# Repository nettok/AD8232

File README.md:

# AD8232
Single Lead Heart Rate Monitor Circuit Board

DO NOT USE!  This is just an exercise on building a simple PCB based on the following original board from SparkFun: https://www.sparkfun.com/products/12650

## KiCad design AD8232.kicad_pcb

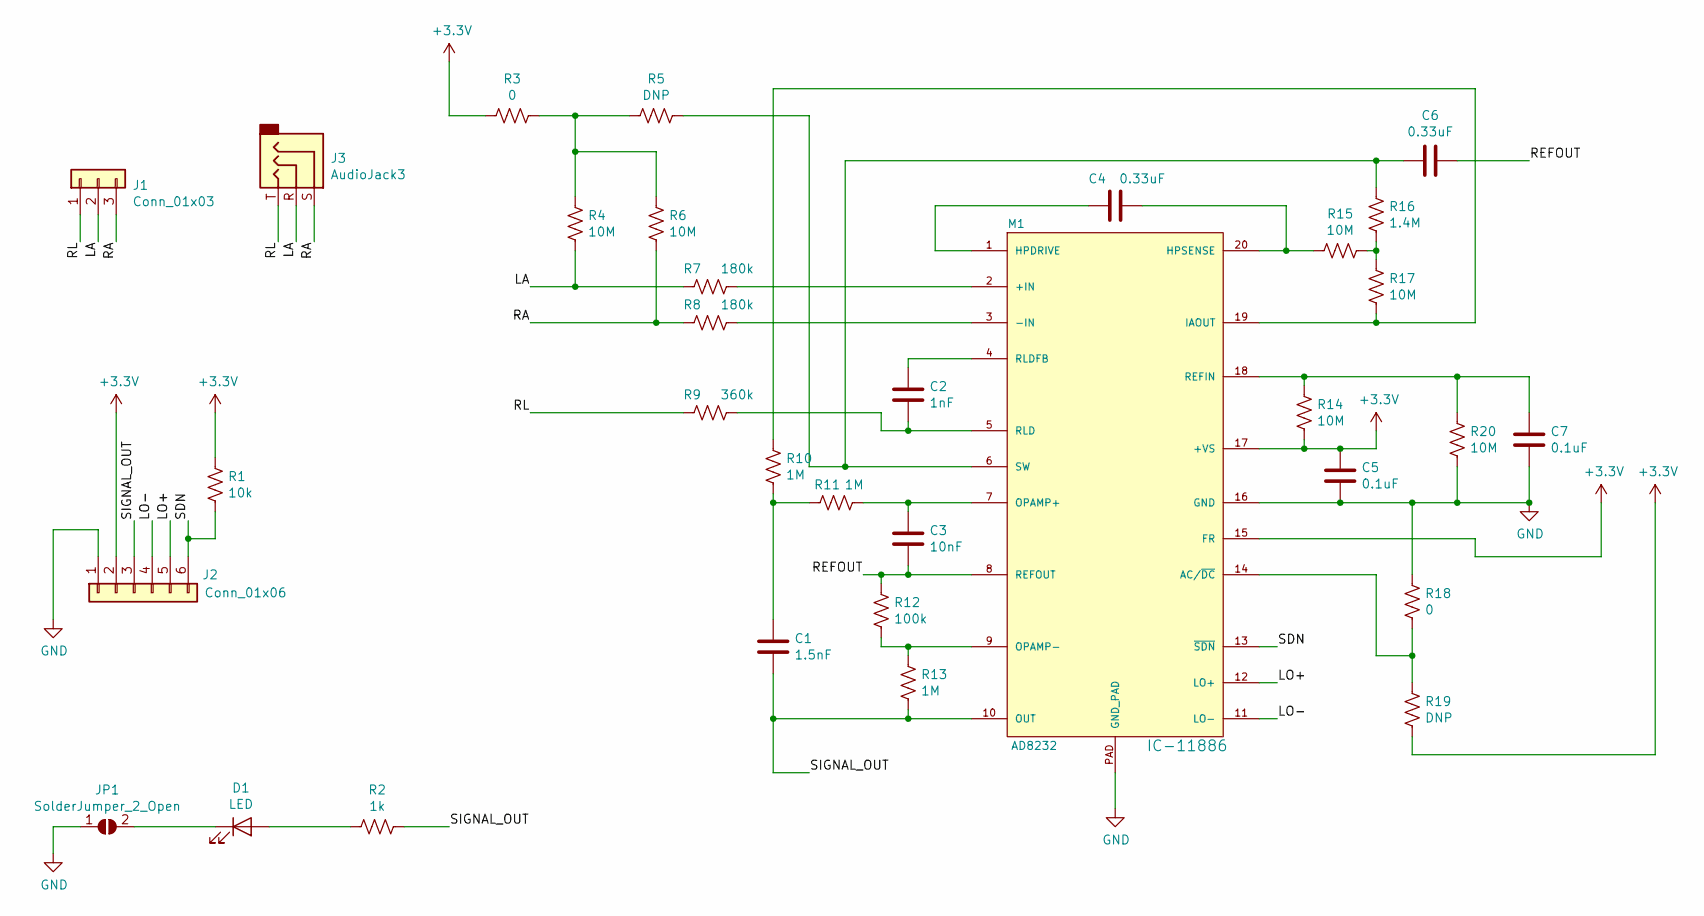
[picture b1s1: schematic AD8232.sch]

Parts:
C1: 1.5nF; C_0603_1608Metric
C2: 1nF; C_0603_1608Metric
C3: 10nF; C_0603_1608Metric
C4, C6: 0.33uF; C_0805_2012Metric
C5, C7: 0.1uF; C_0603_1608Metric
D1: LED; LED_0603_1608Metric
J1: Conn_01x03; 1X03
J2: Conn_01x06; 1X06
J3: AudioJack3; Jack_3.5mm_CUI_SJ-3523-SMT_Horizontal
JP1: SolderJumper_2_Open; SolderJumper-2_P1.3mm_Open_RoundedPad1.0x1.5mm
M1: AD8232; LFCSP_20
R1: 10k; R_0603_1608Metric
R2: 1k; R_0603_1608Metric
R3, R18: 0; R_0603_1608Metric
R4, R6, R14, R15, R17, R20: 10M; R_0603_1608Metric
R5, R19: DNP; R_0603_1608Metric
R7, R8: 180k; R_0603_1608Metric
R9: 360k; R_0603_1608Metric
R10, R11, R13: 1M; R_0603_1608Metric
R12: 100k; R_0603_1608Metric
R16: 1.4M; R_0603_1608Metric

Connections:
+3V3: C5.2, J2.2, M1.15 (FR), M1.17 (+VS), R1.1, R3.2, R14.2, R19.1
/LA: J1.2, J3.R, R4.2, R7.2
/LO+: J2.5, M1.12 (LO+)
/LO-: J2.4, M1.11 (LO-)
/RA: J1.3, J3.S, R6.2, R8.2
/REFOUT: C3.2, C6.1, M1.8 (REFOUT), R12.1
/RL: J1.1, J3.T, R9.2
/SDN: J2.6, M1.13 (~SDN), R1.2
/SIGNAL_OUT: C1.2, J2.3, M1.10 (OUT), R2.1, R13.2
GND: C5.1, C7.1, J2.1, JP1.1 (A), M1.16 (GND), M1.PAD (GND_PAD), R18.2, R20.1
unnamed: C1.1, R10.2, R11.2
unnamed: C2.1, M1.4 (RLDFB)
unnamed: C2.2, M1.5 (RLD), R9.1
unnamed: C3.1, M1.7 (OPAMP+), R11.1
unnamed: C4.1, M1.20 (HPSENSE), R15.2
unnamed: C4.2, M1.1 (HPDRIVE)
unnamed: C6.2, M1.6 (SW), R5.1, R16.2
unnamed: C7.2, M1.18 (REFIN), R14.1, R20.2
unnamed: D1.1 (K), JP1.2 (B)
unnamed: D1.2 (A), R2.2
unnamed: M1.2 (+IN), R7.1
unnamed: M1.3 (-IN), R8.1
unnamed: M1.9 (OPAMP-), R12.2, R13.1
unnamed: M1.14 (AC/~DC), R18.1, R19.2
unnamed: M1.19 (IAOUT), R10.1, R17.1
unnamed: R3.1, R4.1, R5.2, R6.1
unnamed: R15.1, R16.1, R17.2

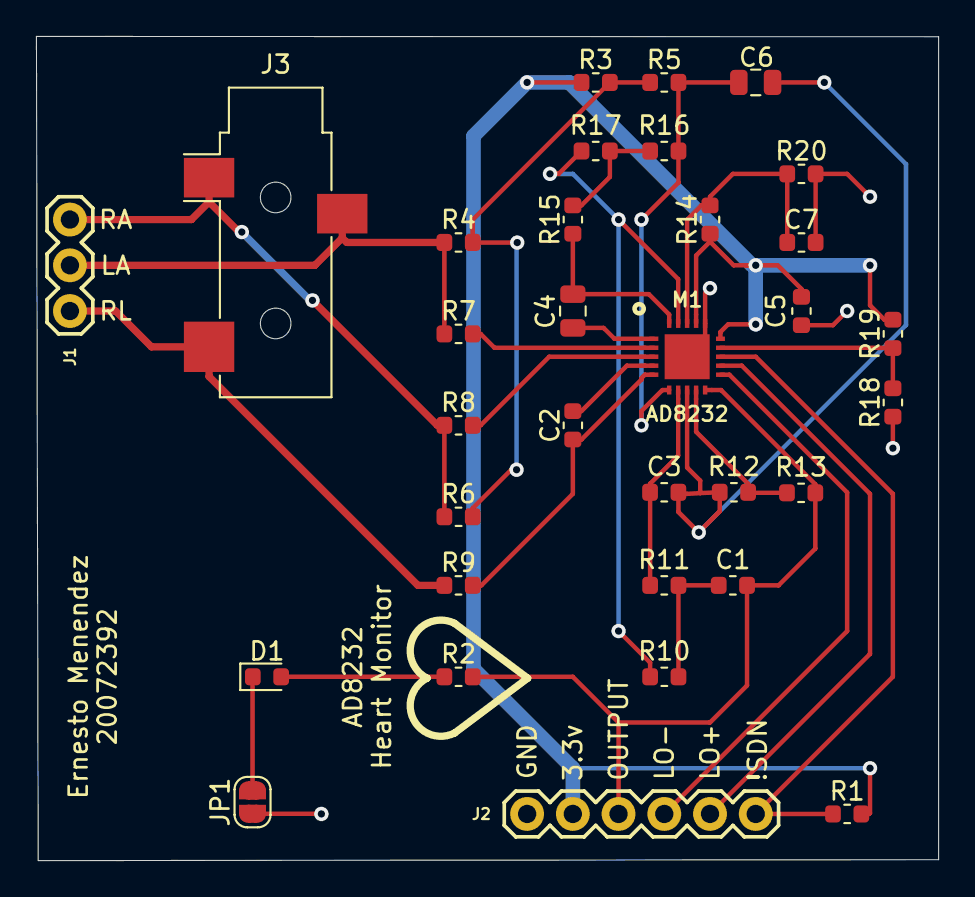
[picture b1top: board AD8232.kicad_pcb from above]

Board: 2 copper layers, 50.1 x 45.8 mm, 33 parts (0 on the bottom side), 27 nets.

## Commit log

2020-03-15 primer commit
2020-03-16 agregar simbolos al esquematico
2020-03-17 conectar simbolos en el esquematico
2020-03-22 anotar simbolos del esquema
2020-03-22 agregar huellas a los simbolos en el esquematico
2020-03-22 agregar huella de SparkFun para LFCSP_20 y usar en AD8232
2020-03-23 initialize PCB with schematic
2020-03-24 usar huellas de conectores 1x03 y 1x06 de SparkFun
2020-03-26 primera colocacacion de componentes en el PCB
2020-04-03 agregar pistas al PCB, excluyendo GND y REFOUT
2020-04-03 agregar pistas de +3.3v pendientes
2020-04-03 agregar pistas de REFOUT
2020-04-03 conectar GND
2020-04-03 definir corte de orilla de PCB
2020-04-03 mover via para que no que sobrepuesta con pista de alimentacion
2020-04-03 agregar y ordenar silk screen del PCB
2020-04-04 definir configuracion del margen de la mascara de soldadura en PCB
2020-04-04 generar archivos gerber
2020-04-04 agregar archivo de taladrado
2020-04-04 cambiar ajuster de configuracion de trazado de archivos gerber
2020-04-04 corregir conexion a GND del integrado AD8232, y volver a generar los archivos gerber
